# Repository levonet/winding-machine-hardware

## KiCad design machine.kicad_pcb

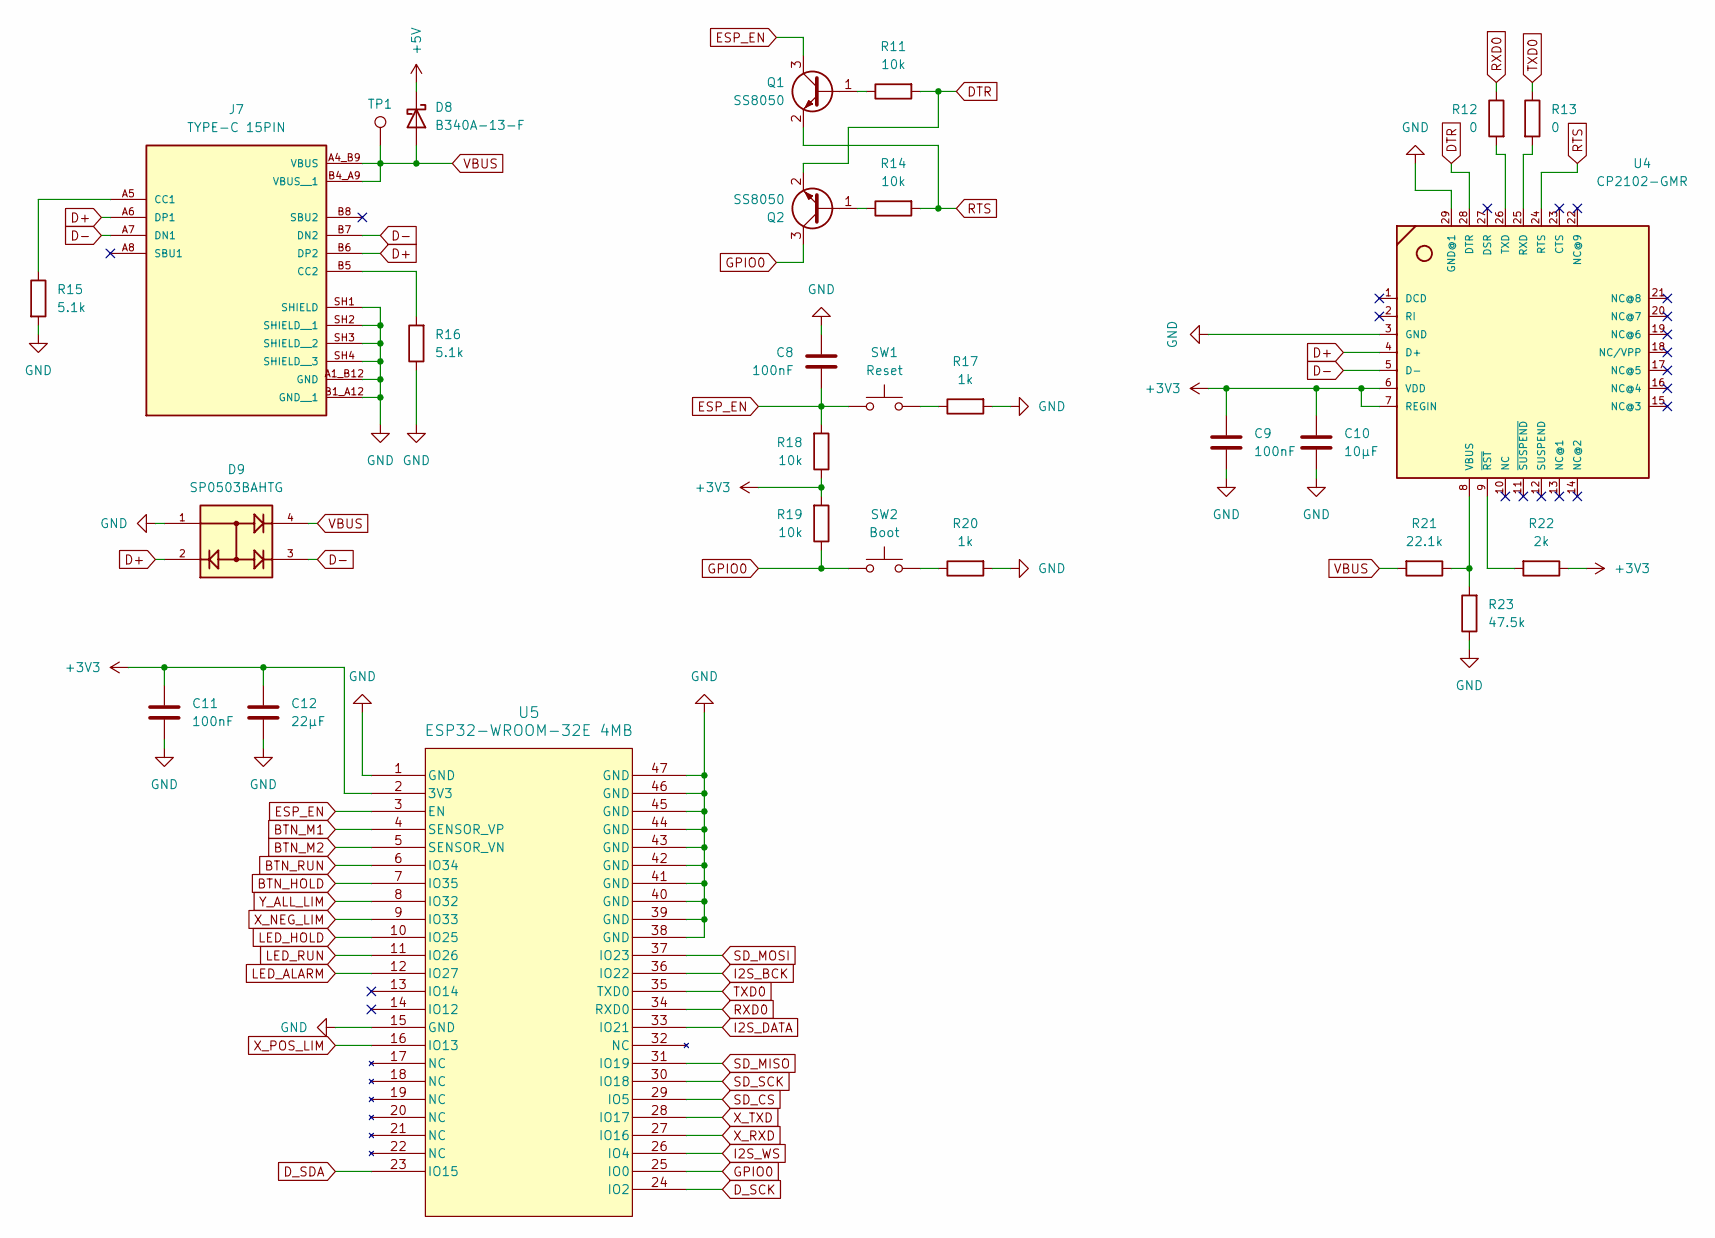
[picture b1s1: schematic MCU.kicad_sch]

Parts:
C8, C9, C11: 100nF; C_0805_2012Metric_Pad1.18x1.45mm_HandSolder
C10: 10μF; C_0805_2012Metric_Pad1.18x1.45mm_HandSolder
C12: 22μF; C_0805_2012Metric_Pad1.18x1.45mm_HandSolder
D8: B340A-13-F; D_SMC
D9: SP0503BAHTG; SOT143; PARTREV N/A
J7: TYPE-C 15PIN; AMPHENOL_10155435-00011LF; PARTREV C
Q1, Q2: SS8050; SOT-23
R11, R14, R18, R19: 10k; R_0805_2012Metric_Pad1.20x1.40mm_HandSolder
R12, R13: 0; R_0805_2012Metric_Pad1.20x1.40mm_HandSolder
R15, R16: 5.1k; R_0805_2012Metric_Pad1.20x1.40mm_HandSolder
R17, R20: 1k; R_0805_2012Metric_Pad1.20x1.40mm_HandSolder
R21: 22.1k; R_0805_2012Metric_Pad1.20x1.40mm_HandSolder
R22: 2k; R_0805_2012Metric_Pad1.20x1.40mm_HandSolder
R23: 47.5k; R_0805_2012Metric_Pad1.20x1.40mm_HandSolder
SW1: Reset; SW_Push_SPST_NO_Alps_SKRK
SW2: Boot; SW_Push_SPST_NO_Alps_SKRK
TP1: TestPoint_Pad_D1.0mm
U4: CP2102-GMR; QFN28G_0.5-5X5MM; MPN CP2102-GMR
U5: ESP32-WROOM-32E 4MB; ESP32-WROOM-32E_EXP

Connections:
+3V3: C9.2, C10.2, C11.2, C12.2, R18.1, R19.2, R22.1, U4.6 (VDD), U4.7 (REGIN), U5.2 (3V3); also elsewhere on the board
+5V: D8.1 (K); also elsewhere on the board
BTN_HOLD: U5.7 (IO35); also elsewhere on the board
BTN_M1: U5.4 (SENSOR_VP); also elsewhere on the board
BTN_M2: U5.5 (SENSOR_VN); also elsewhere on the board
BTN_RUN: U5.6 (IO34); also elsewhere on the board
D+: D9.2, J7.A6 (DP1), J7.B6 (DP2), U4.4 (D+)
D-: D9.3, J7.A7 (DN1), J7.B7 (DN2), U4.5 (D-)
DTR: Q2.2 (E), R11.2, U4.28 (DTR)
D_SCK: U5.24 (IO2); also elsewhere on the board
D_SDA: U5.23 (IO15); also elsewhere on the board
ESP_EN: C8.1, Q1.3 (C), R18.2, SW1.2, U5.3 (EN)
GND: C8.2, C9.1, C10.1, C11.1, C12.1, D9.1, J7.A1_B12 (GND), J7.B1_A12 (GND__1), J7.SH1 (SHIELD), J7.SH2 (SHIELD__1), J7.SH3 (SHIELD__2), J7.SH4 (SHIELD__3), R15.2, R16.1, R17.2, R20.2, R23.1, U4.3 (GND), U4.29 (GND@1), U5.1 (GND), U5.15 (GND), U5.38 (GND), U5.39 (GND), U5.40 (GND), U5.41 (GND), U5.42 (GND), U5.43 (GND), U5.44 (GND), U5.45 (GND), U5.46 (GND), U5.47 (GND); also elsewhere on the board
GPIO0: Q2.3 (C), R19.1, SW2.2, U5.25 (IO0)
I2S_BCK: U5.36 (IO22); also elsewhere on the board
I2S_DATA: U5.33 (IO21); also elsewhere on the board
I2S_WS: U5.26 (IO4); also elsewhere on the board
LED_ALARM: U5.12 (IO27); also elsewhere on the board
LED_HOLD: U5.10 (IO25); also elsewhere on the board
LED_RUN: U5.11 (IO26); also elsewhere on the board
unnamed: J7.A5 (CC1), R15.1
unnamed: J7.B5 (CC2), R16.2
unnamed: Q1.1 (B), R11.1
unnamed: Q2.1 (B), R14.1
unnamed: R17.1, SW1.1
unnamed: R20.1, SW2.1
unnamed: R13.2, U4.25 (RXD)
unnamed: R12.2, U4.26 (TXD)
unnamed: R21.1, R23.2, U4.8 (VBUS)
unnamed: R22.2, U4.9 (~RST)
RTS: Q1.2 (E), R14.2, U4.24 (RTS)
RXD0: R12.1, U5.34 (RXD0)
SD_CS: U5.29 (IO5); also elsewhere on the board
SD_MISO: U5.31 (IO19); also elsewhere on the board
SD_MOSI: U5.37 (IO23); also elsewhere on the board
SD_SCK: U5.30 (IO18); also elsewhere on the board
TXD0: R13.1, U5.35 (TXD0)
VBUS: D8.2 (A), D9.4, J7.A4_B9 (VBUS), J7.B4_A9 (VBUS__1), R21.2, TP1.1
X_NEG_LIM: U5.9 (IO33); also elsewhere on the board
X_POS_LIM: U5.16 (IO13); also elsewhere on the board
X_RXD: U5.27 (IO16); also elsewhere on the board
X_TXD: U5.28 (IO17); also elsewhere on the board
Y_ALL_LIM: U5.8 (IO32); also elsewhere on the board

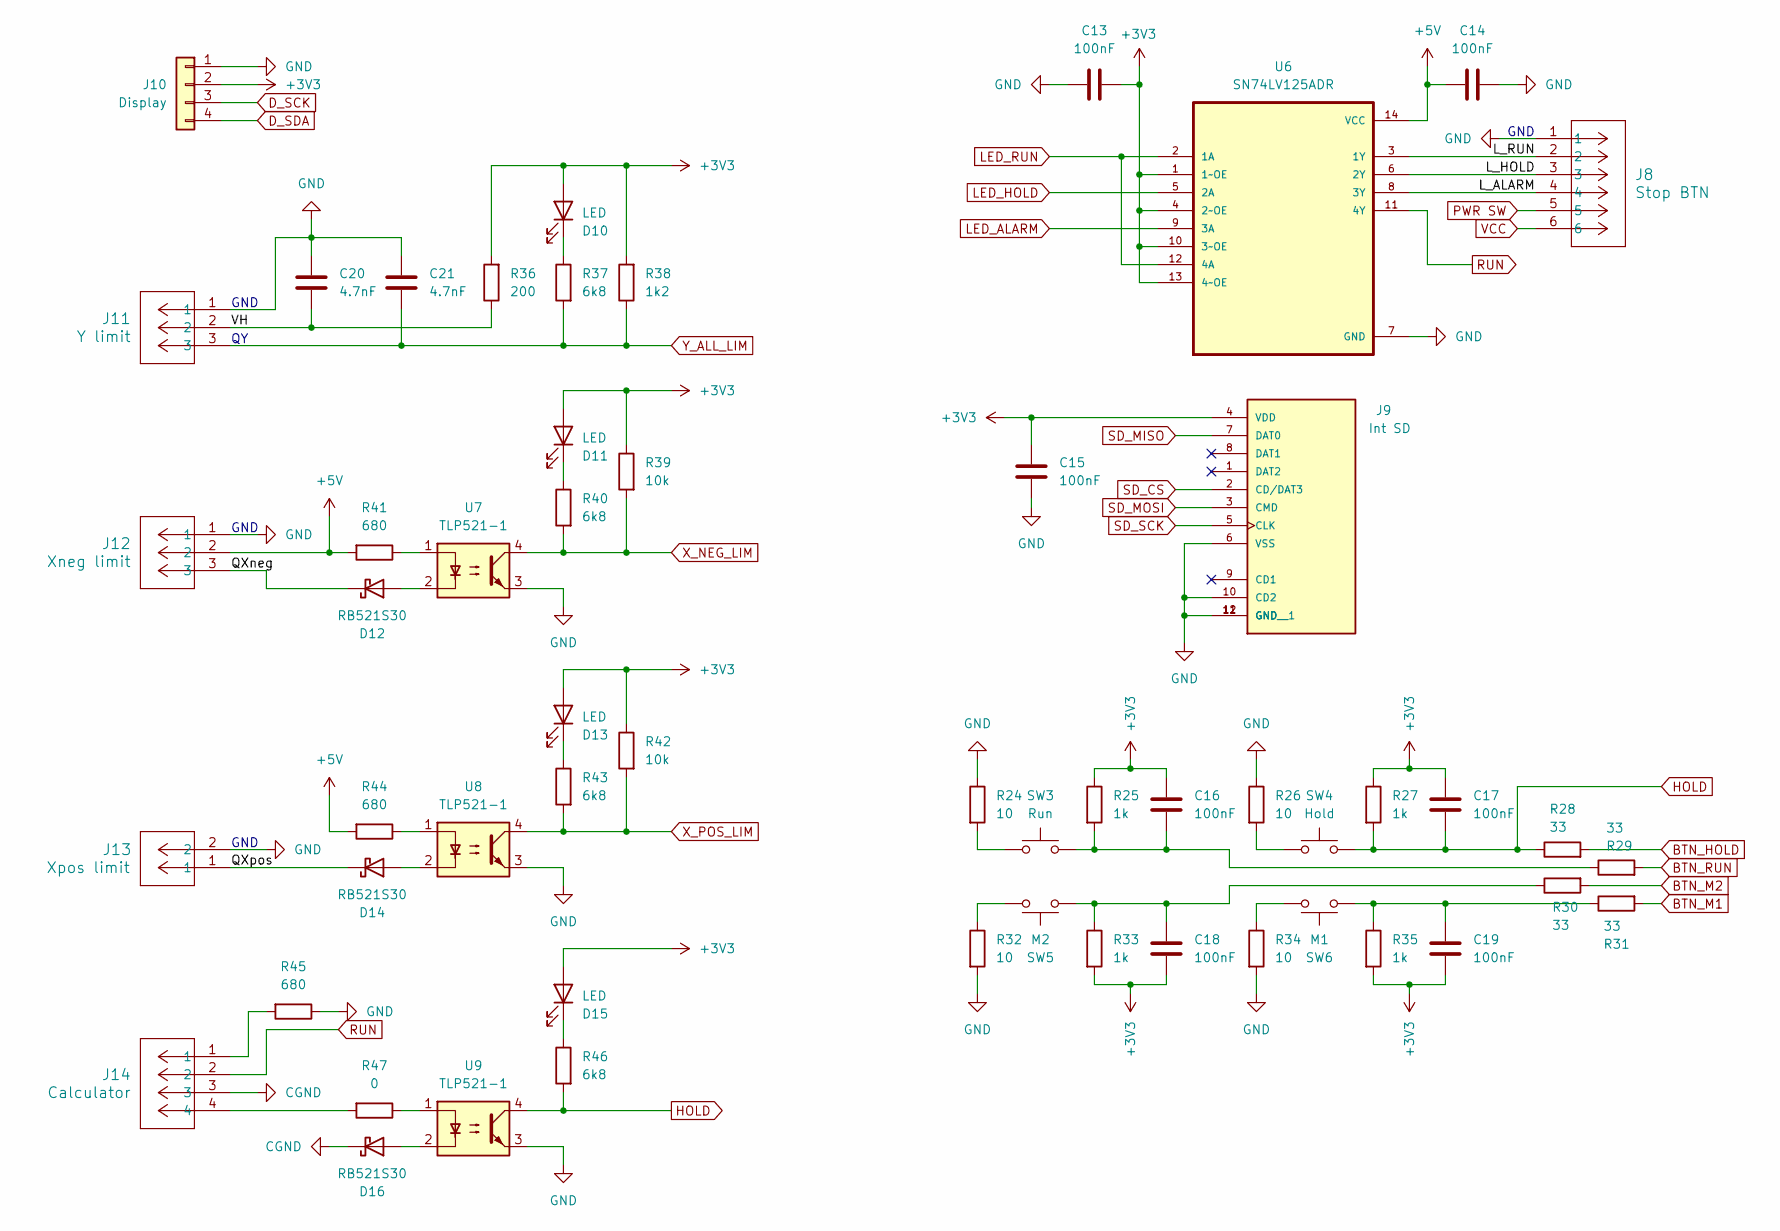
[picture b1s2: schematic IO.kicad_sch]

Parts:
C13, C14, C15, C16, C17, C18, C19: 100nF; C_0805_2012Metric_Pad1.18x1.45mm_HandSolder
C20, C21: 4.7nF; C_0805_2012Metric_Pad1.18x1.45mm_HandSolder
D10, D11, D13, D15: LED; LED_0603_1608Metric
D12, D14, D16: RB521S30; D_SOD-523
J8: Stop BTN; CONN_B6B-XH-A_JST
J9: Int SD; GCT_MEM2061-01-188-00-A_REVA
J10: Display; PinSocket_1x04_P2.54mm_Vertical
J11: Y limit; CONN_B3B-XH-A_JST
J12: Xneg limit; CONN_B3B-XH-A_JST
J13: Xpos limit; CONN_B2B-XH-A_JST
J14: Calculator; CONN_B4B-XH-A_JST
R24, R26, R32, R34: 10; R_0805_2012Metric_Pad1.20x1.40mm_HandSolder
R25, R27, R33, R35: 1k; R_0805_2012Metric_Pad1.20x1.40mm_HandSolder
R28, R29, R30, R31: 33; R_0805_2012Metric_Pad1.20x1.40mm_HandSolder
R36: 200; R_0805_2012Metric_Pad1.20x1.40mm_HandSolder
R37, R40, R43, R46: 6k8; R_0805_2012Metric_Pad1.20x1.40mm_HandSolder
R38: 1k2; R_0805_2012Metric_Pad1.20x1.40mm_HandSolder
R39, R42: 10k; R_0805_2012Metric_Pad1.20x1.40mm_HandSolder
R41, R44, R45: 680; R_0805_2012Metric_Pad1.20x1.40mm_HandSolder
R47: 0; R_0805_2012Metric_Pad1.20x1.40mm_HandSolder
SW3: Run; SW_SPST_Omron_B3F-40xx
SW4: Hold; SW_SPST_Omron_B3F-40xx
SW5: M2; SW_SPST_Omron_B3F-40xx
SW6: M1; SW_SPST_Omron_B3F-40xx
U6: SN74LV125ADR; SOIC127P600X175-14N
U7, U8, U9: TLP521-1; TLP521SM_ISO

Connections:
+3V3: C13.2, C15.2, C16.2, C17.2, C18.1, C19.1, D10.2 (A), D11.2 (A), D13.2 (A), D15.2 (A), J9.4 (VDD), J10.2, R25.1, R27.1, R33.2, R35.2, R36.2, R38.2, R39.1, R42.1, U6.1 (1~OE), U6.4 (2~OE), U6.10 (3~OE), U6.13 (4~OE); also elsewhere on the board
+5V: C14.1, J12.2, R41.2, R44.2, U6.14 (VCC); also elsewhere on the board
/IO/L_ALARM: J8.4, U6.8 (3Y)
/IO/L_HOLD: J8.3, U6.6 (2Y)
/IO/L_RUN: J8.2, U6.3 (1Y)
/IO/QXneg: D12.1 (K), J12.3
/IO/QXpos: D14.1 (K), J13.1
/IO/VH: C20.2, J11.2, R36.1
BTN_HOLD: R28.2; also elsewhere on the board
BTN_M1: R31.2; also elsewhere on the board
BTN_M2: R30.2; also elsewhere on the board
BTN_RUN: R29.2; also elsewhere on the board
CGND: D16.1 (K), J14.3
D_SCK: J10.3; also elsewhere on the board
D_SDA: J10.4; also elsewhere on the board
GND: C13.1, C14.2, C15.1, C20.1, C21.1, J8.1, J9.6 (VSS), J9.10 (CD2), J9.11 (GND), J9.12 (GND__1), J10.1, J11.1, J12.1, J13.2, R24.1, R26.1, R32.2, R34.2, R45.1, U6.7 (GND), U7.3, U8.3, U9.3; also elsewhere on the board
HOLD: C17.1, R27.2, R28.1, R46.2, SW4.1, U9.4
LED_ALARM: U6.9 (3A); also elsewhere on the board
LED_HOLD: U6.5 (2A); also elsewhere on the board
LED_RUN: U6.2 (1A), U6.12 (4A); also elsewhere on the board
unnamed: C16.1, R25.2, R29.1, SW3.1
unnamed: C18.2, R30.1, R33.1, SW5.1
unnamed: C19.2, R31.1, R35.1, SW6.1
unnamed: D10.1 (K), R37.1
unnamed: D11.1 (K), R40.1
unnamed: D12.2 (A), U7.2
unnamed: D13.1 (K), R43.1
unnamed: D14.2 (A), U8.2
unnamed: D15.1 (K), R46.1
unnamed: D16.2 (A), U9.2
unnamed: J14.1, R45.2
unnamed: J14.4, R47.2
unnamed: R24.2, SW3.2
unnamed: R26.2, SW4.2
unnamed: R32.1, SW5.2
unnamed: R34.1, SW6.2
unnamed: R41.1, U7.1
unnamed: R44.1, U8.1
unnamed: R47.1, U9.1
PWR SW: J8.5; also elsewhere on the board
RUN: J14.2, U6.11 (4Y)
SD_CS: J9.2 (CD/DAT3); also elsewhere on the board
SD_MISO: J9.7 (DAT0); also elsewhere on the board
SD_MOSI: J9.3 (CMD); also elsewhere on the board
SD_SCK: J9.5 (CLK); also elsewhere on the board
VCC: J8.6; also elsewhere on the board
X_NEG_LIM: R39.2, R40.2, U7.4; also elsewhere on the board
X_POS_LIM: R42.2, R43.2, U8.4; also elsewhere on the board
Y_ALL_LIM: C21.2, J11.3, R37.2, R38.1; also elsewhere on the board

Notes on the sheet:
GND

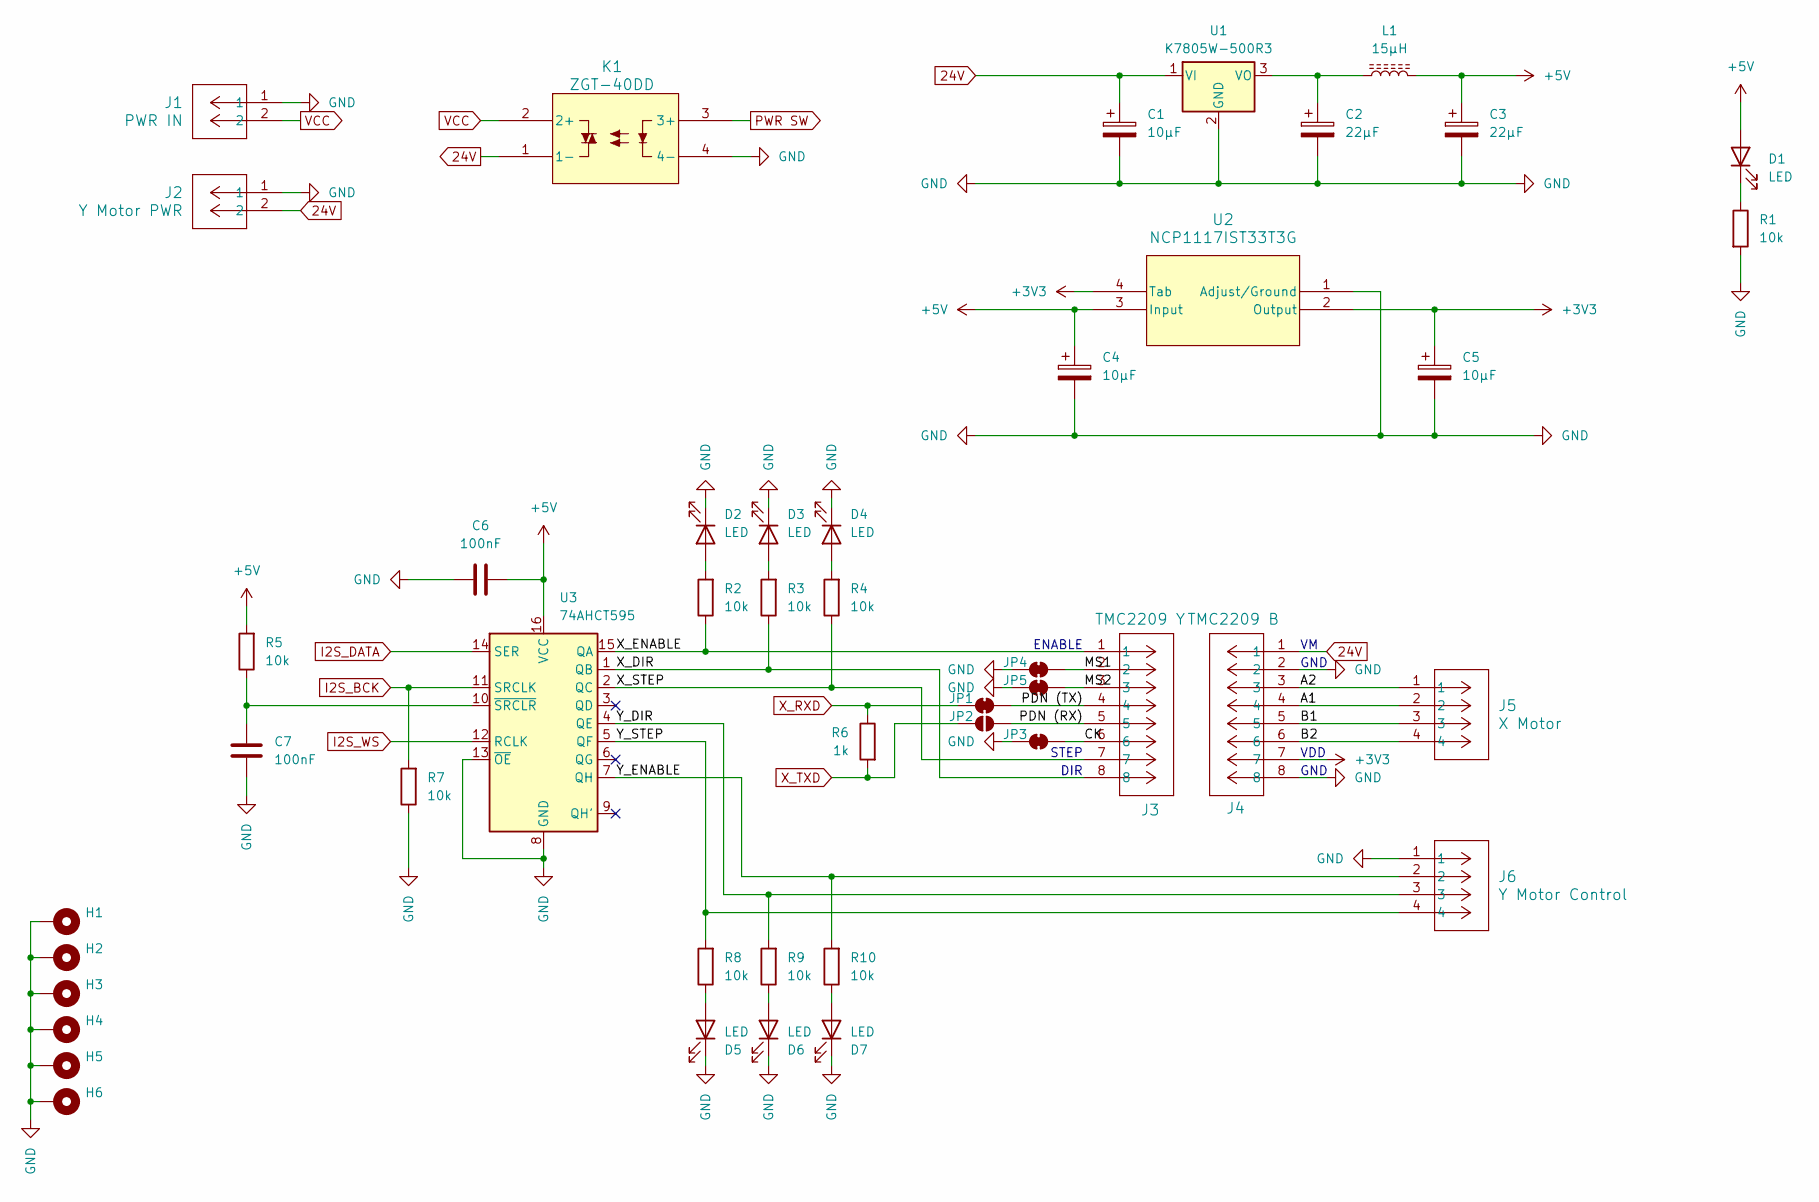
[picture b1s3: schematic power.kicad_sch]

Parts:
C1, C4, C5: 10μF; CP_EIA-6032-28_Kemet-C_HandSolder
C2, C3: 22μF; CP_EIA-3528-21_Kemet-B_HandSolder
C6, C7: 100nF; C_0805_2012Metric_Pad1.18x1.45mm_HandSolder
D1, D2, D3, D4, D5, D6, D7: LED; LED_0603_1608Metric
H1, H2, H3, H4, H5, H6: MountingHole_3.2mm_M3_DIN965_Pad
J1: PWR IN; PhoenixContact_MSTBVA_2,5_2-G-5,08_1x02_P5.08mm_Vertical
J2: Y Motor PWR; PhoenixContact_MSTBVA_2,5_2-G-5,08_1x02_P5.08mm_Vertical
J3: TMC2209 Y; CONN8_LFBN-RC_SUL
J4: TMC2209 B; CONN8_LFBN-RC_SUL
J5: X Motor; CONN_B4B-XH-A_JST
J6: Y Motor Control; CONN_B4B-XH-A_JST
JP1: PDN; SolderJumper-2_P1.3mm_Bridged_RoundedPad1.0x1.5mm
JP2: PDN; SolderJumper-2_P1.3mm_Open_RoundedPad1.0x1.5mm
JP3: CK; SolderJumper-2_P1.3mm_Bridged_RoundedPad1.0x1.5mm
JP4: MS1; SolderJumper-2_P1.3mm_Bridged_RoundedPad1.0x1.5mm
JP5: MS2; SolderJumper-2_P1.3mm_Bridged_RoundedPad1.0x1.5mm
K1: ZGT-40DD; SSR_DCDC
L1: 15μH; L_SXN_SMDRI74
R1, R2, R3, R4, R5, R7, R8, R9, R10: 10k; R_0805_2012Metric_Pad1.20x1.40mm_HandSolder
R6: 1k; R_0805_2012Metric_Pad1.20x1.40mm_HandSolder
U1: K7805W-500R3; TO-220-3_Vertical
U2: NCP1117IST33T3G; SOT-223_NCP1117IST33T3G_OSI
U3: 74AHCT595; TSSOP-16_4.4x5mm_P0.65mm

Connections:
24V: C1.1, J2.2, J4.1, K1.1 (1-), U1.1 (VI)
+3V3: C5.1, J4.7, U2.2 (Output), U2.4 (Tab); also elsewhere on the board
+5V: C3.1, C4.1, C6.1, D1.2 (A), L1.2, R5.2, U2.3 (Input), U3.16 (VCC); also elsewhere on the board
/Power/A1: J4.4, J5.2
/Power/A2: J4.3, J5.1
/Power/B1: J4.5, J5.3
/Power/B2: J4.6, J5.4
/Power/CK: J3.6, JP3.1 (A)
/Power/MS1: J3.2, JP4.1 (A)
/Power/MS2: J3.3, JP5.1 (A)
/Power/PDN (RX): J3.5, JP2.1 (A)
/Power/PDN (TX): J3.4, JP1.1 (A)
/Power/X_DIR: J3.8, R3.1, U3.1 (QB)
/Power/X_ENABLE: J3.1, R2.1, U3.15 (QA)
/Power/X_STEP: J3.7, R4.1, U3.2 (QC)
/Power/Y_DIR: J6.3, R9.2, U3.4 (QE)
/Power/Y_ENABLE: J6.2, R10.2, U3.7 (QH)
/Power/Y_STEP: J6.4, R8.2, U3.5 (QF)
GND: C1.2, C2.2, C3.2, C4.2, C5.2, C6.2, C7.1, D2.1 (K), D3.1 (K), D4.1 (K), D5.1 (K), D6.1 (K), D7.1 (K), H1.1, H2.1, H3.1, H4.1, H5.1, H6.1, J1.1, J2.1, J4.2, J4.8, J6.1, JP3.2 (B), JP4.2 (B), JP5.2 (B), K1.4 (4-), R1.2, R7.1, U1.2 (GND), U2.1 (Adjust/Ground), U3.8 (GND), U3.13 (~OE); also elsewhere on the board
I2S_BCK: R7.2, U3.11 (SRCLK); also elsewhere on the board
I2S_DATA: U3.14 (SER); also elsewhere on the board
I2S_WS: U3.12 (RCLK); also elsewhere on the board
unnamed: D1.1 (K), R1.1
unnamed: D2.2 (A), R2.2
unnamed: D3.2 (A), R3.2
unnamed: D4.2 (A), R4.2
unnamed: D5.2 (A), R8.1
unnamed: D6.2 (A), R9.1
unnamed: D7.2 (A), R10.1
unnamed: C2.1, L1.1, U1.3 (VO)
unnamed: C7.2, R5.1, U3.10 (~SRCLR)
PWR SW: K1.3 (3+); also elsewhere on the board
VCC: J1.2, K1.2 (2+); also elsewhere on the board
X_RXD: JP1.2 (B), R6.1; also elsewhere on the board
X_TXD: JP2.2 (B), R6.2; also elsewhere on the board

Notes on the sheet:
DIR
ENABLE
GND
VDD
STEP

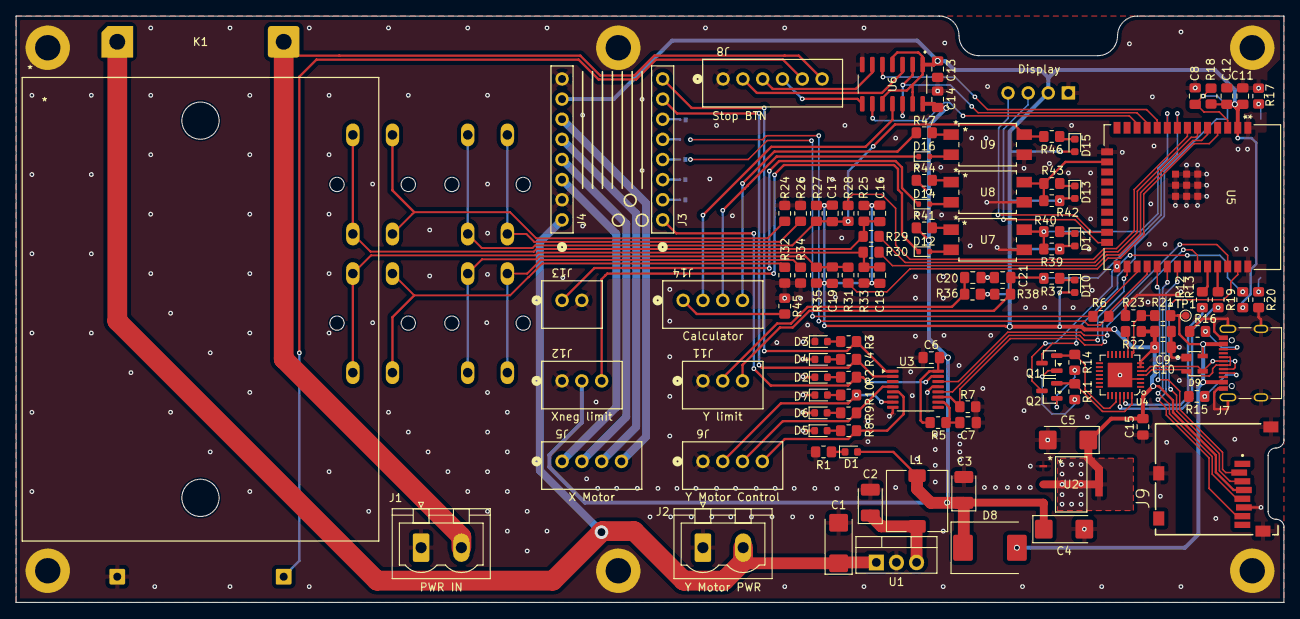
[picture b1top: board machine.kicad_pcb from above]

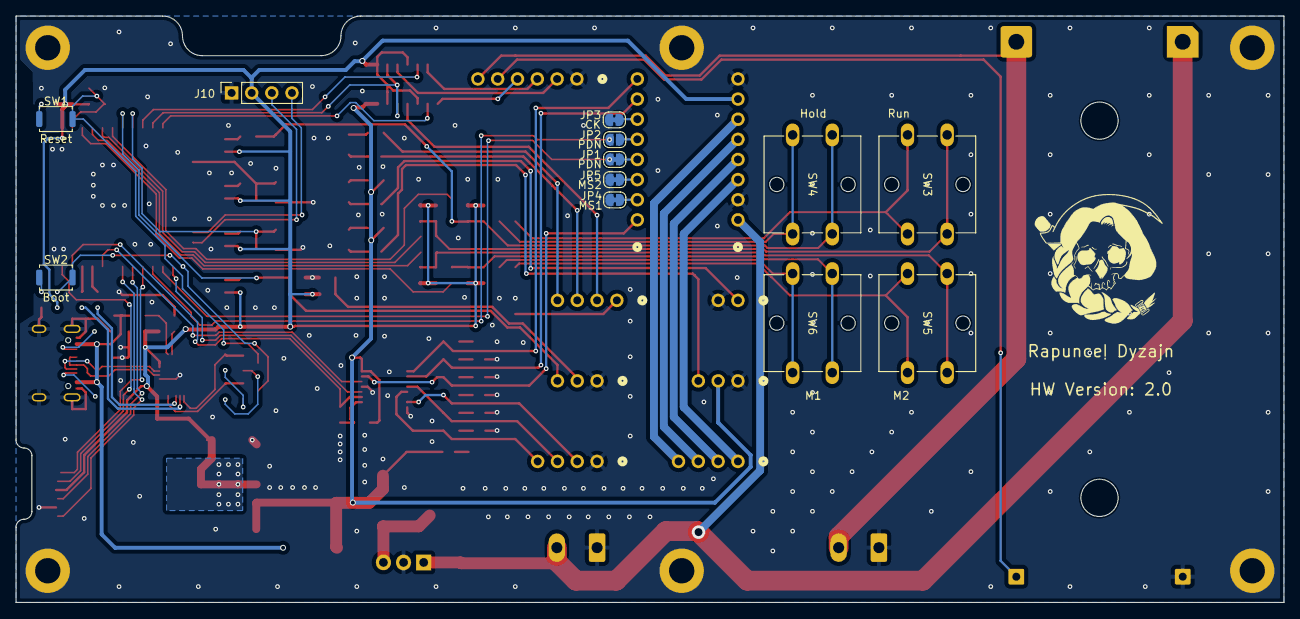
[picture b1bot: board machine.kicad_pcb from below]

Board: 2 copper layers, 160.0 x 74.0 mm, 129 parts (12 on the bottom side), 98 nets.

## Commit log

2025-03-25 Init
2025-03-26 Add buttons pcb
2025-03-26 Gerber generation
2025-09-24 Add stability
2025-09-27 Migration init
2025-09-28 Transformation in progress
2025-10-14 Finalization v2.0
